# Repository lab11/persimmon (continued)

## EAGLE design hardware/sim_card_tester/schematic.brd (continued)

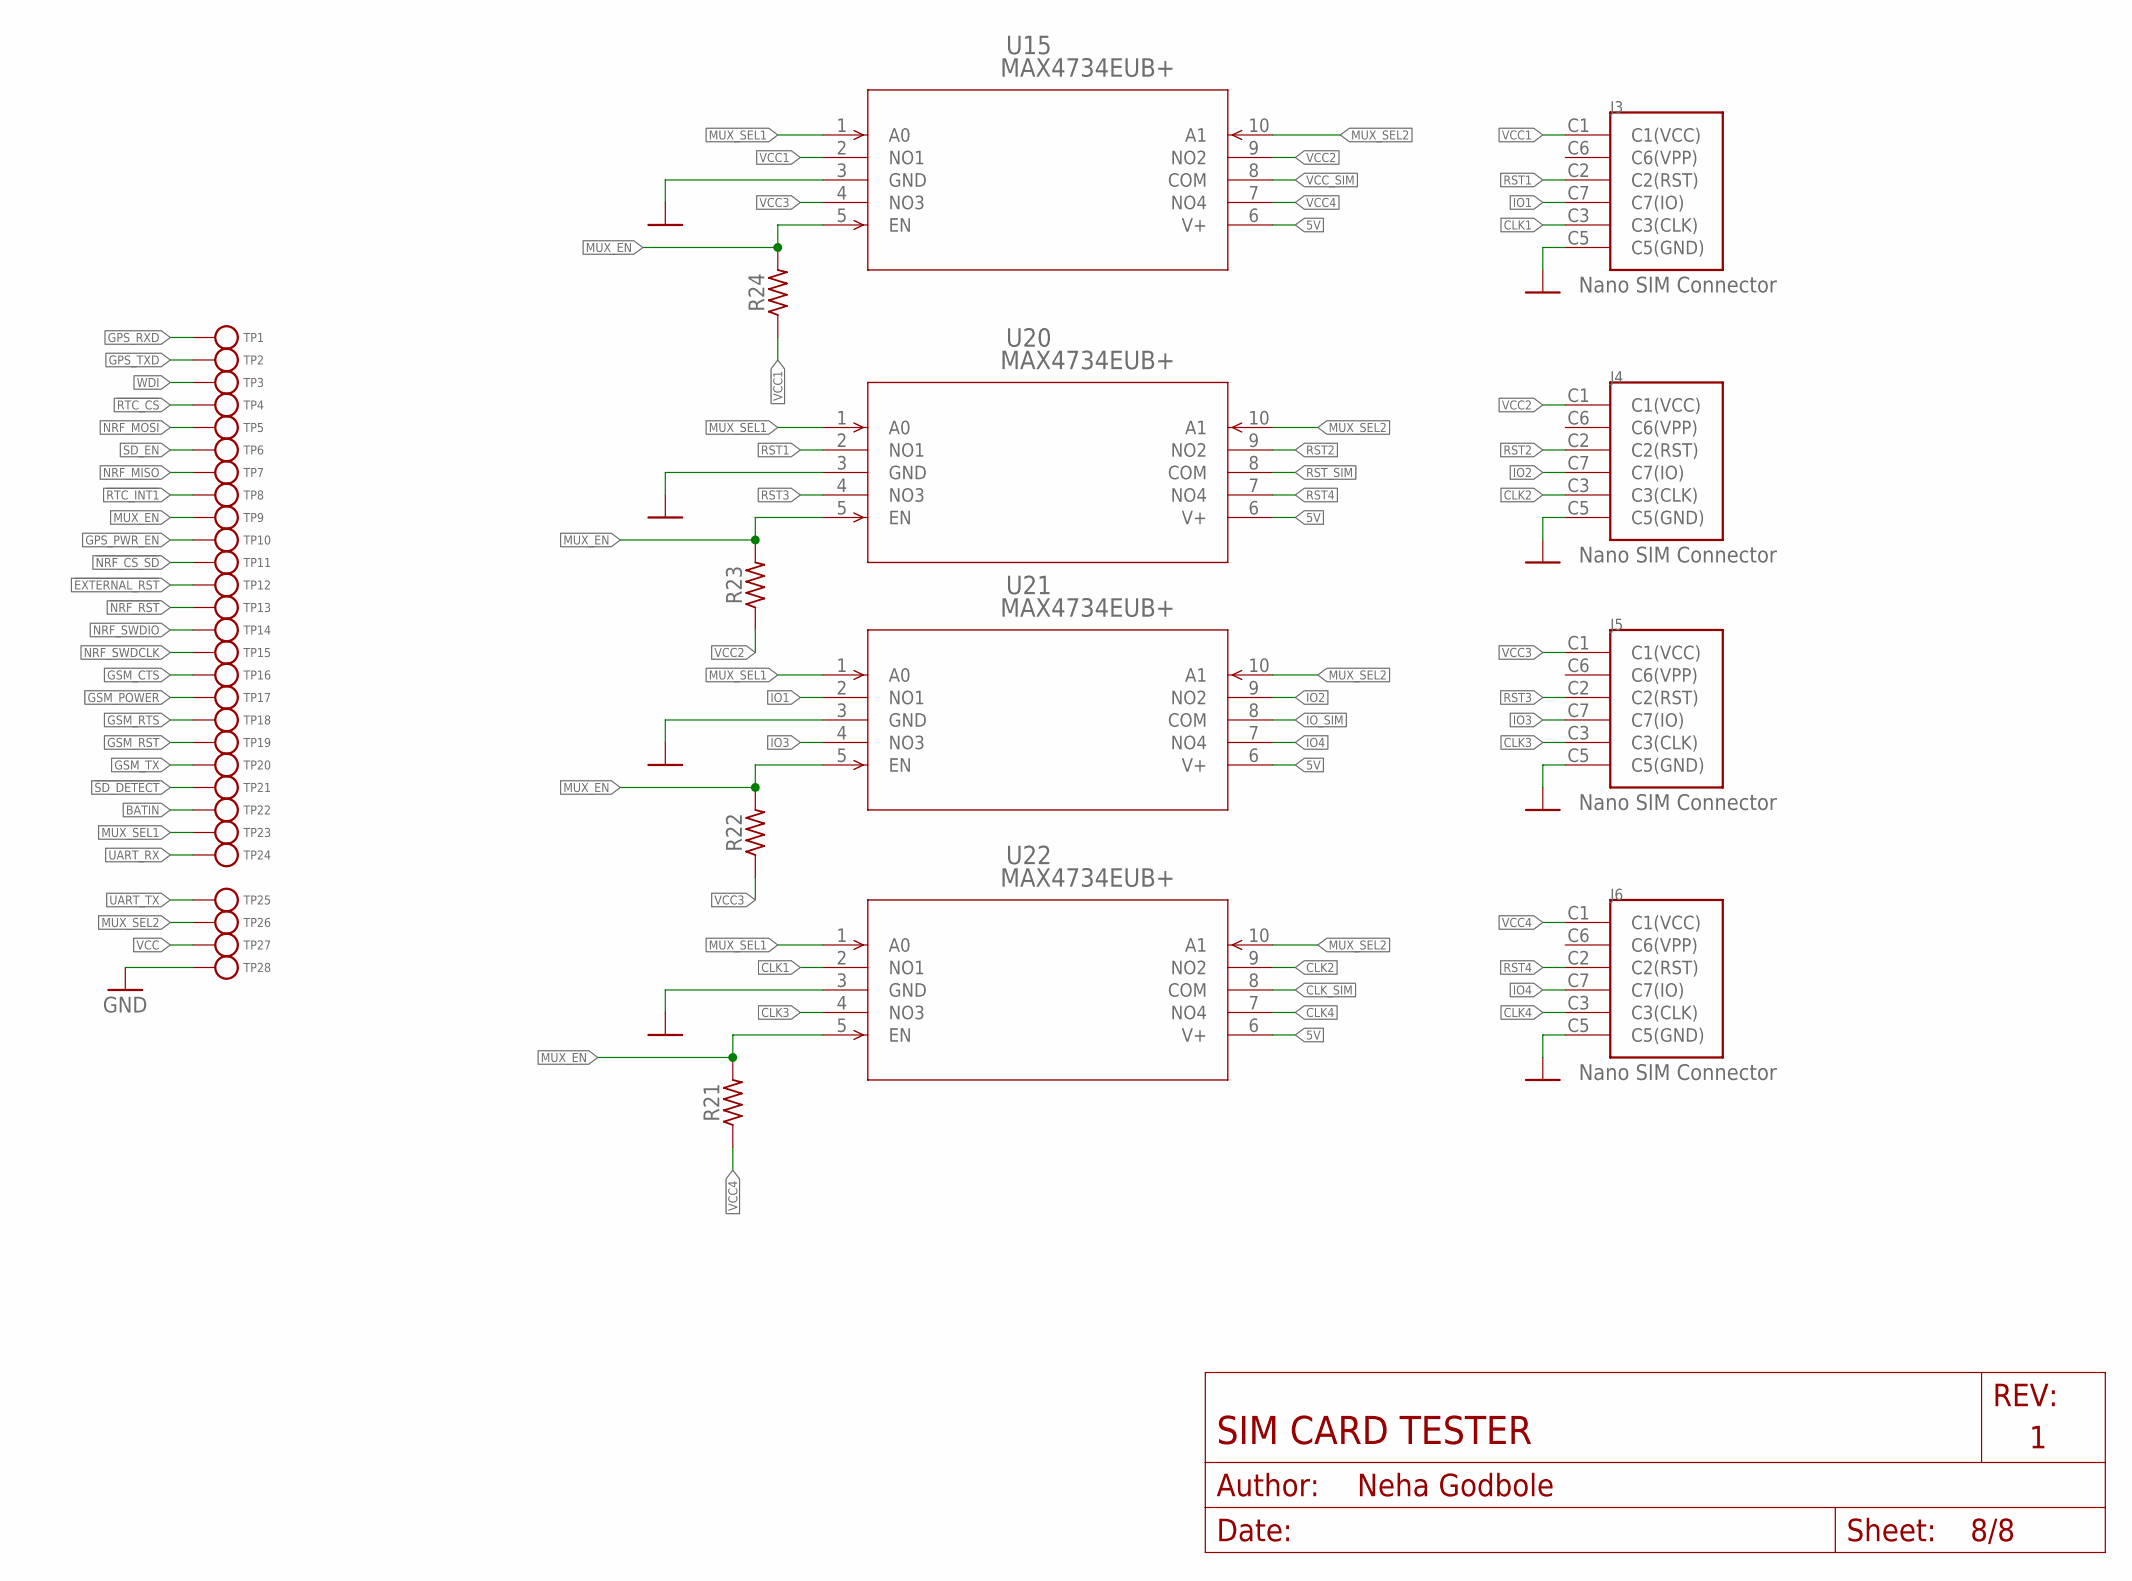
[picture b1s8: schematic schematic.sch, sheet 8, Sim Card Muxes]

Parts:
J3, J4, J5, J6: NANO_SIM; WURTH_NANO_SIM
R21, R22, R23, R24: 10k; R0603; MPN RC0603JR-0710KL; DIGIKEY 311-10KGRCT-ND
TP1, TP2, TP3, TP4, TP5, TP6, TP7, TP8, TP9, TP10, TP11, TP12, TP13, TP14, TP15, TP16, TP17, TP18, TP19, TP20, TP21, TP22, TP23, TP24, TP25, TP26, TP27, TP28: TEST-POINT; PAD.03X.03
U15, U20, U21, U22: MAX4734EUB+; 21-0061L

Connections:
5V: U15.6 (V+), U20.6 (V+), U21.6 (V+), U22.6 (V+); also elsewhere on the board
!EXTERNAL_RST: TP12.P$1; also elsewhere on the board
!NRF_CS_SD: TP11.P$1; also elsewhere on the board
!NRF_RST: TP13.P$1; also elsewhere on the board
!RTC_CS: TP4.P$1; also elsewhere on the board
!RTC_INT1: TP8.P$1; also elsewhere on the board
!SD_DETECT: TP21.P$1; also elsewhere on the board
BATIN: TP22.P$1; also elsewhere on the board
CLK1: J3.C3 (C3(CLK)), U22.2 (NO1)
CLK2: J4.C3 (C3(CLK)), U22.9 (NO2)
CLK3: J5.C3 (C3(CLK)), U22.4 (NO3)
CLK4: J6.C3 (C3(CLK)), U22.7 (NO4)
CLK_SIM: U22.8 (COM); also elsewhere on the board
GND: J3.C5 (C5(GND)), J4.C5 (C5(GND)), J5.C5 (C5(GND)), J6.C5 (C5(GND)), TP28.P$1, U15.3 (GND), U20.3 (GND), U21.3 (GND), U22.3 (GND); also elsewhere on the board
GPS_PWR_EN: TP10.P$1; also elsewhere on the board
GPS_RXD: TP1.P$1; also elsewhere on the board
GPS_TXD: TP2.P$1; also elsewhere on the board
GSM_CTS: TP16.P$1; also elsewhere on the board
GSM_POWER: TP17.P$1; also elsewhere on the board
GSM_RST: TP19.P$1; also elsewhere on the board
GSM_RTS: TP18.P$1; also elsewhere on the board
GSM_TX: TP20.P$1; also elsewhere on the board
IO1: J3.C7 (C7(IO)), U21.2 (NO1)
IO2: J4.C7 (C7(IO)), U21.9 (NO2)
IO3: J5.C7 (C7(IO)), U21.4 (NO3)
IO4: J6.C7 (C7(IO)), U21.7 (NO4)
IO_SIM: U21.8 (COM); also elsewhere on the board
MUX_EN: R21.2, R22.2, R23.2, R24.2, TP9.P$1, U15.5 (EN), U20.5 (EN), U21.5 (EN), U22.5 (EN); also elsewhere on the board
MUX_SEL1: TP23.P$1, U15.1 (A0), U20.1 (A0), U21.1 (A0), U22.1 (A0); also elsewhere on the board
MUX_SEL2: TP26.P$1, U15.10 (A1), U20.10 (A1), U21.10 (A1), U22.10 (A1); also elsewhere on the board
NRF_MISO: TP7.P$1; also elsewhere on the board
NRF_MOSI: TP5.P$1; also elsewhere on the board
NRF_SWDCLK: TP15.P$1; also elsewhere on the board
NRF_SWDIO: TP14.P$1; also elsewhere on the board
RST1: J3.C2 (C2(RST)), U20.2 (NO1)
RST2: J4.C2 (C2(RST)), U20.9 (NO2)
RST3: J5.C2 (C2(RST)), U20.4 (NO3)
RST4: J6.C2 (C2(RST)), U20.7 (NO4)
RST_SIM: U20.8 (COM); also elsewhere on the board
SD_EN: TP6.P$1; also elsewhere on the board
UART_RX: TP24.P$1; also elsewhere on the board
UART_TX: TP25.P$1; also elsewhere on the board
VCC: TP27.P$1; also elsewhere on the board
VCC1: J3.C1 (C1(VCC)), R24.1, U15.2 (NO1)
VCC2: J4.C1 (C1(VCC)), R23.1, U15.9 (NO2)
VCC3: J5.C1 (C1(VCC)), R22.1, U15.4 (NO3)
VCC4: J6.C1 (C1(VCC)), R21.1, U15.7 (NO4)
VCC_SIM: U15.8 (COM); also elsewhere on the board
WDI: TP3.P$1; also elsewhere on the board

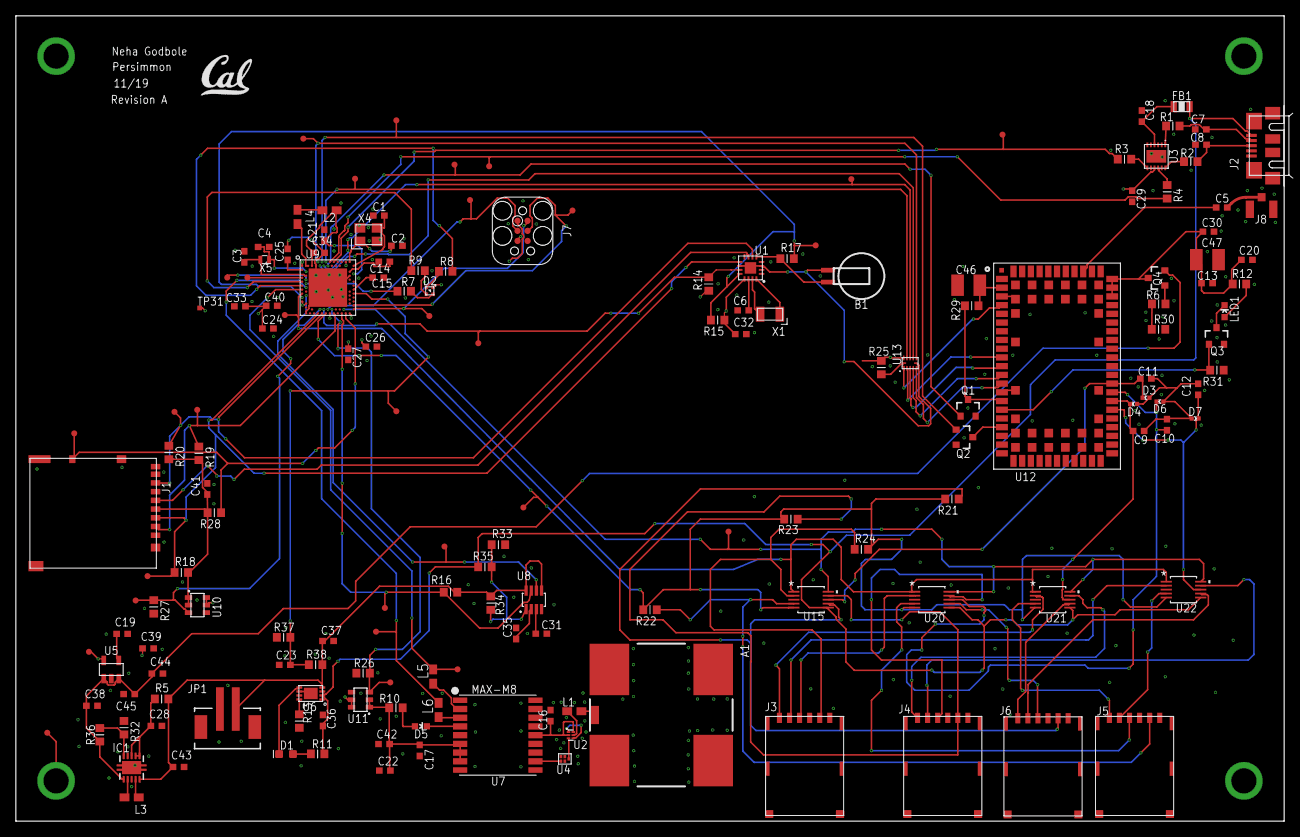
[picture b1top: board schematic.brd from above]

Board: 4 copper layers, 160.0 x 101.6 mm, 168 parts (0 on the bottom side), 122 nets.

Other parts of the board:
U$3: UCB_CAL_200MIL

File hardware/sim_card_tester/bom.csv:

Qty,Value,Device,Package,Parts,Description,DIGIKEY,MANUFACTURER,MF,MOUSER,MPN,NEWARK,OC_FARNELL,OC_NEWARK,POPULARITY,SPICEPREFIX,TP_SIGNAL_NAME,VENDOR
1,,M024UCON-15767,JST-2-SMD-VERT,JP1,,455-1734-1-ND,JST Sales America Inc.,,,B2B-PH-SM4-TB(LF)(SN),,,,,,,
1,,MS518SE,MS518SE-FL35E,B1,,,,,,,,,,,,,
9,0.1uF,CAPACITOR_0603_L,RESC0603_L,"C22, C23, C24, C25, C26, C27,C28, C29, C30",Capacitor,490-5405-1-ND,Murata Electronics,,,GRM033R61A104ME15D,,,,,,,
1,0.82uF,CAPACITOR_0603_L,RESC0603_L,C31,Capacitor,399-3117-1-ND,KEMET,,,C0603C824K8PACTU,,,,,,,
1,1.3M,R-US_R0603,R0603,R36,Resistor,YAG3326CT-ND,Yageo,,,RC0603FR-071M3L,,,,,,,
4,100,R-US_R0603,R0603,"R3, R4, R5, R6",Resistor,311-100HRCT-ND,Yageo,,,RC0603FR-07100RL,,,,,,,
6,100k,R-US_R0603,R0603,"R26, R27, R28, R29, R30, R31",Resistor,311-100KGRCT-ND,Yageo,,,RC0603JR-07100KL,,,,,,,
1,100pF,CAPACITOR_0603_L,RESC0603_L,C14,Capacitor,311-1069-1-ND,Yageo,,,CC0603JRNPO9BN101,,,,,,,
1,100uF,C-USC1210,C1210,C46,Capacitor,490-9969-1-ND,Murata Electronics,,,GRM32ER61A107ME20L,,,,,,,
1,10M,R-US_R0603,R0603,R38,Resistor,311-10MGRCT-ND,Yageo,,,RC0603JR-0710ML,,,,,,,
12,10k,R-US_R0603,R0603,"R14, R15, R16, R17, R18, R19, R20, R21, R22, R23, R24, R25",Resistor,311-10KGRCT-ND,Yageo,,,RC0603JR-0710KL,,,,,,,
5,10nF,CAPACITOR_0603_L,RESC0603_L,"C16, C17, C18, C19, C20",Capacitor,490-7194-1-ND,Murata Electronics,,,GRM033R61E103KA12D,,,,,,,
4,10uF,CAPACITOR_0603_L,RESC0603_L,"C42, C43, C44, C45",Capacitor,490-12538-1-ND,Murata Electronics,,,GRM188R60J106KE47D,,,,,,,
1,10uH,INDUCTOR_0603_M,RESC0603_M,L4,Generic chip inductor,587-1720-1-ND,Taiyo Yuden,,,CBMF1608T100K,,,,,,,
4,12pF,CAPACITOR_0603_L,RESC0603_L,"C1, C2, C3, C4",Capacitor,311-1059-1-ND,Yageo,,,CC0603JRNPO9BN120,,,,,,,
4,14V,DIODE_ZENER0402,0402_DIODE,"D1, D2, D3, D4",Diode,_PESD0402-140CT-ND,Littlefuse,,,_PESD0402-140,,,,,,,
1,15nH,INDUCTOR_0603_M,RESC0603_M,L2,Generic chip inductor,490-15648-1-ND,Murata Electronics,,,LQW18AN15NG8ZD,,,,,,,
1,1M,R-US_R0603,R0603,R35,Resistor,311-1.00MHRCT-ND,Murata Electronics,,,RC0603FR-071ML,,,,,,,
2,1k,INDUCTOR_0603_M,RESC0603_M,"L5, L6",Generic chip inductor,490-1015-1-ND,Murata Electronics,,,BLM18AG102SN1D,,,,,,,
3,1k,R-US_R0603,R0603,"R10, R11, R12",Resistor,311-1.0KGRCT-ND,Yageo,,,RC0603JR-071KL,,,,,,,
3,1uF,CAPACITOR_0603_L,RESC0603_L,"C32, C33, C34",Capacitor,399-3118-1-ND,KEMET,,,C0603C105K8PACTU,,,,,,,
1,2.2M,R-US_R0603,R0603,R37,Resistor,311-2.2MGRCT-ND,Yageo,,,RC0603JR-072M2L,,,,,,,
1,2.2uF,CAPACITOR_0603_L,RESC0603_L,C35,Capacitor,490-12738-1-ND,Murata Electronics,,,GRM188R61E225MA12D,,,,,,,
1,2.2uH,INDUCTOR_0603_M,RESC0603_M,L3,Generic chip inductor,490-14478-1-ND,Murata Electronics,,,LQM18PN2R2MGHD,,,,,,,
1,200k,R-US_R0603,R0603,R32,Capacitor,311-200KGRTR-ND,Yageo,,,RC0603JR-07200KL,,,,,,,
1,220uF,C-USC1210,C1210,C47,Capacitor,490-16308-1-ND,Murata Electronics,,,GRM32ER60J227ME05L,,,,,,,
2,27,R-US_R0603,R0603,"R1, R2",Resistor,311-27GRCT-ND,Yageo,,,RC0603JR-0727RL,,,,,,,
1,2k,R-US_R0603,R0603,R13,Resistor,311-2.00KHRCT-ND,Yageo,,,RC0603FR-072KL,,,,,,,
1,32.768kHz,ABS05-32.768KHZ-9-T,ABS05,X5,32.768kHz Crystal,535-11897-1-ND,Abracon,,,ABS05-32.768KHZ-9-T,,,,,,,
1,32MHz,7V-32.000MAHV-T,TXC-7V,X4,TXC CRYSTAL SMD,887-2568-1-ND,TXC CORPORATION,,,7M-32.000MAHV-T,,,,,,,
1,33pF,CAPACITOR_0603_L,RESC0603_L,C5,Capacitor,399-7896-1-ND,KEMET,,,C0603C330J1GACTU,,,,,,,
6,4.7uF,CAPACITOR_0603_L,RESC0603_L,"C36, C37, C38, C39, C40, C41",Capacitor,490-10992-1-ND,Murata Electronics,,,ZRB18AR6YA475KE05L,,,,,,,
3,470,R-US_R0603,R0603,"R7, R8, R9",Capacitor,311-470HRCT-ND,Yageo,,,RC0603FR-07470RL,,,,,,,
1,47nF,CAPACITOR_0603_L,RESC0603_L,C21,Capacitor,490-5854-1-ND,Murata Electronics,,,GCJ188R71H473KA12D,,,,,,,
7,47pF,CAPACITOR_0603_L,RESC0603_L,"C6, C7, C8, C9, C10, C11, C12",Capacitor,311-1065-1-ND,Murata Electronics,,,CC0603JRNPO9BN470,,,,,,,
1,499k,R-US_R0603,R0603,R33,Resistor,311-499KHRCT-ND,Yageo,,,RC0603FR-07499KL,,,,,,,
1,5.6nH,INDUCTOR_0603_M,RESC0603_M,L1,Generic chip inductor,490-15723-1-ND,Murata Electronics,,,LQW18AN5N6G8ZD,,,,,,,
1,56pF,CAPACITOR_0603_L,RESC0603_L,C13,Capacitor,311-1066-1-ND,Yageo,,,CC0603JRNPO9BN560,,,,,,,
1,600,FERRITE_BEAD0805,0805_CAP,FB1,,_240-2390-1-ND,,,,,,,,,,,
1,820pF,CAPACITOR_0603_L,RESC0603_L,C15,Capacitor,311-1189-1-ND,Yageo,,,CC0603KRX7R9BB821,,,,,,,
1,825k,R-US_R0603,R0603,R34,Resistor,311-825KHRCT-ND,Yageo,,,RC0603FR-07825KL,,,,,,,
1,AB1815-T3,AB1815-T3,QFN-16-3MM,U1,Ultra-low current RTC. 55nA quiescent @ 3V. 1.5-3.6V input.,535-11936-1-ND,Abracon,,,AB1815-T3,,,,,,,
1,ABS07-32.768KHZ-7-T,ABS07-32.768KHZ-7-T,2-SMD,X1,32.768kHz Crystal,535-9543-1-ND,ABRACON,,,ABS07-32.768KHZ-7-T ,,,,,,,
1,BGA725L6-ALT,BGA725L6-ALT,LNA-TSLP-6-2-ALT,U2,,BGA725L6E6327FTSA1CT-ND,Infineon,,,BGA725L6E6327FTSA1,,,,,,,
1,BLUE,LED0603,LED-0603,LED1,LED,511-1578-1-ND ,Rohm,,,SML-D12M8WT86,,,,,,,
1,BLUE,LED0603,LED-0603,D5,LED,160-1837-6-ND ,Lite-On Inc.,,,LTST-C194TBKT,,,,,,,
1,CON_MICRO_SDDM3AT-SF-PEJM5,CON_MICRO_SDDM3AT-SF-PEJM5,DM3AT-SF-PEJM5,J1,CONN MICRO SD R/A PUSH-PUSH SMD,HR1964CT-ND,,,,DM3AT-SF-PEJM5,,,,,,,
1,FTDI234XD,FTDI234XD,DFN-12/3MM,U3,FTDI234XD USB to UART Bridge in 3x3 DFN Package,768-1178-1-ND,,,895-FT234XD-R,,53X3171,,,,,,
1,GPS-ANTENNA,GPS-ANTENNA,ANT1818B00BT1516S,A1,,311-1531-ND,Yageo,,,ANT1818B00BT1516S,,,,,,,
1,GREEN,LED0603,LED-0603,D1,LED (Generic),,,,,,,,,,,,
1,MAX-M8,MAX-M8,MAX-M8,U7,,672-1003-1-ND,u-blox,,,MAX-M8Q-0,,,,,,,
4,MAX4734EUB+,MAX4734EUB+,21-0061L,U15,,,,,,,,,,,,,
1,MAX67XXMAX6749MAX67XX,MAX67XXMAX6749MAX67XX,SOT-23-8,U8,A simple watchdog timer with adjustable timeouts and reset time,MAX6749KA+TCT-ND,Maxim Integrated,,,MAX6749KA+T,,,,,,,
1,MAX8887EZK33+T,MAX8887EZK33+T,SOT-23-5,U5,IC REG LDO 3.3V 0.3A TSOT23-5,MAX8887EZK33+TCT-ND,,,,,,,,,,,
1,MCP73831,MCP73831,DFN-8-MCP,U6,Description: Device for MCP73831,,,,,,,,,,,,
1,MICRO_USB_B_HIROSE_ZX62R-B-5P,MICRO_USB_B_HIROSE_ZX62R-B-5P,USB_MICRO_B-HIROSE-ZX62R-B-5P,J2,USB Micro B Connector,H125274CT-ND,,,,,,,,,,,
3,MOSFET-NCHANNELSMD,MOSFET-NCHANNELSMD,SOT23-3,Q1,,,,,,,,,,,,,
4,NANO_SIM,NANO_SIM,WURTH_NANO_SIM,J3,,,,,,,,,,,,,
1,NRF52840,NRF52840,AQFN73,U9,ultra-low power 2.4 GHz wireless system on chip (SoC) integrating a multiprotocol 2.4 GHz transceiver,,,,,,,,,,,,
1,SAFFB1G56KB0F0A,FILTERS,QCS5I,U4,,587-3990-1-ND,Taiyo Yuden,,,F6QA1G582H2JM-J,,,,,,,
1,SI223DDS,SI223DDS,SOT23-3,Q4,6A SOT-23 P Fet,SI2333DDS-T1-GE3CT-ND,Vishay Siliconix,,,SI2333DDS-T1-GE3,,,,,,,
2,SIP32510,SIP32510,TSOT23-6,U10,,,,,,,,,,,,,
1,SML-LX0404SIUPGUSB,SML-LX0404SIUPGUSB,1MM_SQ_4PAD,D2,1mm^2 RGB LED,67-2125-1-ND,Lumex Opto,,,SML-LX0404SIUPGUSB,,,,,,,
1,TC2030-JLINK-L,TC2030-JLINK-L,TC2030-IDC,J7,,,,,,,,,,,,,
30,TEST-POINT,TEST-POINT,PAD.03X.03,TP1,,,,,,,,,,,,,
1,TPS6300,TPS6300,DRC-S-PVSON-N10,IC1,HIGH EFFICIENT SINGLE INDUCTOR BUCK-BOOST CONVERTER WITH 1.8-A SWITCHES,,,,,TPS63000DRCTG4,,1511852,59M7217,,,,
1,TPTP06SQ,TPTP06SQ,TP06SQ,TP31,Test pad,,,,,,,,,,,,
1,TXB0104RUT,TXB0104RUT,UQFN-12,U13,4-channel bidirectional level translater,296-25888-1-ND,TI,,,TXB0104RUTR,,,,,,,
1,U.FL-R-SMT,U.FL-R-SMT,U.FL_SMT,J8,U.FL-R-SMT Antenna Connector,H122041-ND,Hirose,,,U.FL-R-SMT-1(01),,,,,,,
1,UBLOX_SARA_G350,UBLOX_SARA_G350,UBLOX_SARA_G3,U12,Sara G350 2.5G Radio Module,,,,,,,,,,,,

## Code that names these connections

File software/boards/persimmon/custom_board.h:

// Pin definitions for nRF52 development kit (PCA10040)

#pragma once

#include "nrf_gpio.h"

// LED
#define LEDS_NUMBER 3
#define LEDS_ACTIVE_STATE 0
#define LED_1 NRF_GPIO_PIN_MAP(0,4)
#define LED_2 NRF_GPIO_PIN_MAP(0,5)
#define LED_3 NRF_GPIO_PIN_MAP(0,6)
#define LEDS_INV_MASK LEDS_MASK
#define LEDS_LIST { LED_1, LED_2, LED_3 }
#define BSP_LED_0 LED_1
#define BSP_LED_1 LED_2
#define BSP_LED_2 LED_3

// BUTTONS
#define BUTTONS_NUMBER 0
#define BUTTON_PULL 0

// UART
#define UART_TXD NRF_GPIO_PIN_MAP(1,15)
#define UART_RXD NRF_GPIO_PIN_MAP(1,13)

// GPS
#define GPS_RXD NRF_GPIO_PIN_MAP(0,7)
#define GPS_TXD NRF_GPIO_PIN_MAP(0,8)
#define GPS_PWR_EN NRF_GPIO_PIN_MAP(0,19)

// SPI
#define SPI_MISO NRF_GPIO_PIN_MAP(0,15)
#define SPI_MOSI NRF_GPIO_PIN_MAP(0,13)
#define SPI_SCLK NRF_GPIO_PIN_MAP(0,27)


#define CS_SD NRF_GPIO_PIN_MAP(0,20)
#define SD_DETECT NRF_GPIO_PIN_MAP(1,0)
#define SD_ENABLE NRF_GPIO_PIN_MAP(0,14)

// Hardware Watchdog
#define HW_WDI NRF_GPIO_PIN_MAP(0,11)
#define EXT_RST NRF_GPIO_PIN_MAP(0,24)

// Multiplexers
#define MUX_EN NRF_GPIO_PIN_MAP(0,17)
#define MUX_SEL1 NRF_GPIO_PIN_MAP(1,9)
#define MUX_SEL2 NRF_GPIO_PIN_MAP(0,25)

// Radio
#define GSM_CTS NRF_GPIO_PIN_MAP(0,2)
#define GSM_POWER NRF_GPIO_PIN_MAP(0,3)
#define GSM_RTS NRF_GPIO_PIN_MAP(0,28)
#define GSM_RST NRF_GPIO_PIN_MAP(0,29)
#define GSM_RX NRF_GPIO_PIN_MAP(0,30)
#define GSM_TX NRF_GPIO_PIN_MAP(0,31)

#define BATIN NRF_GPIO_PIN_MAP(1,6)

#define NRF_RST NRF_GPIO_PIN_MAP(0,18)

//compatbility with softdevice

#define SD_CARD_ENABLE      SD_ENABLE
#define SD_CARD_SPI_CS      CS_SD
#define SD_CARD_SPI_MISO    SPI_MISO
#define SD_CARD_SPI_MOSI    SPI_MOSI
#define SD_CARD_SPI_SCLK    SPI_SCLK

#define SD_CARD_SPI_INSTANCE    NRF_SPI1

//RTC
#define RTC_CS      NRF_GPIO_PIN_MAP(0,12)
#define RTC_IRQ1    NRF_GPIO_PIN_MAP(0,16)
#define RTC_IRQ2    NRF_GPIO_PIN_MAP(0,0)
#define RTC_IRQ3    NRF_GPIO_PIN_MAP(0,0)
#define RTC_WDI     NRF_GPIO_PIN_MAP(0,0)

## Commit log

2019-09-03 Create LICENSE
    add license
2019-09-04 first pcb
2019-09-14 second pcb
2019-10-02 fixed schematic and nrf routing
2019-10-09 fixed most things
2019-10-22 fixed via and pad problem
2019-10-22 commit before renumber
2019-10-29 fixed drc errors
2019-11-02 add ground vias, label parts, clean up board
2019-11-02 renumbered
2019-11-02 fixed some wires
2019-11-03 updated parts for caps
2019-11-03 parts for resistors
2019-11-03 added most of the parts
2019-11-03 renumbering again
2019-11-03 fixed numbering
2019-11-12 cleaned up wires
2019-11-17 added test points
2019-11-18 updated bom
2019-11-19 adding zip files
2020-01-09 adding software folder
2020-01-13 sd card tests
2020-09-27 updating test files
